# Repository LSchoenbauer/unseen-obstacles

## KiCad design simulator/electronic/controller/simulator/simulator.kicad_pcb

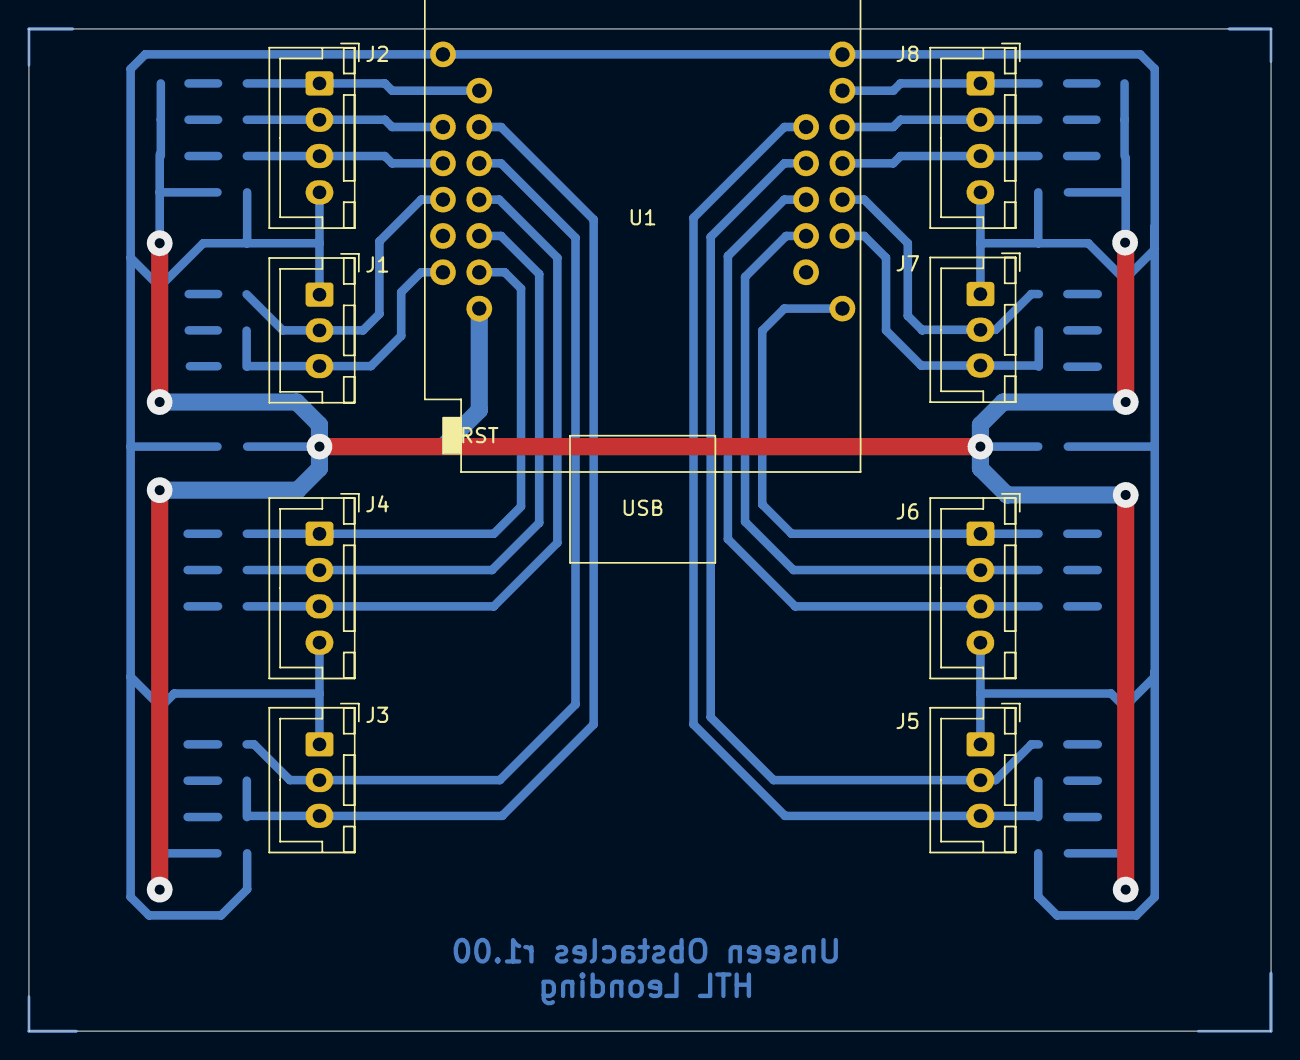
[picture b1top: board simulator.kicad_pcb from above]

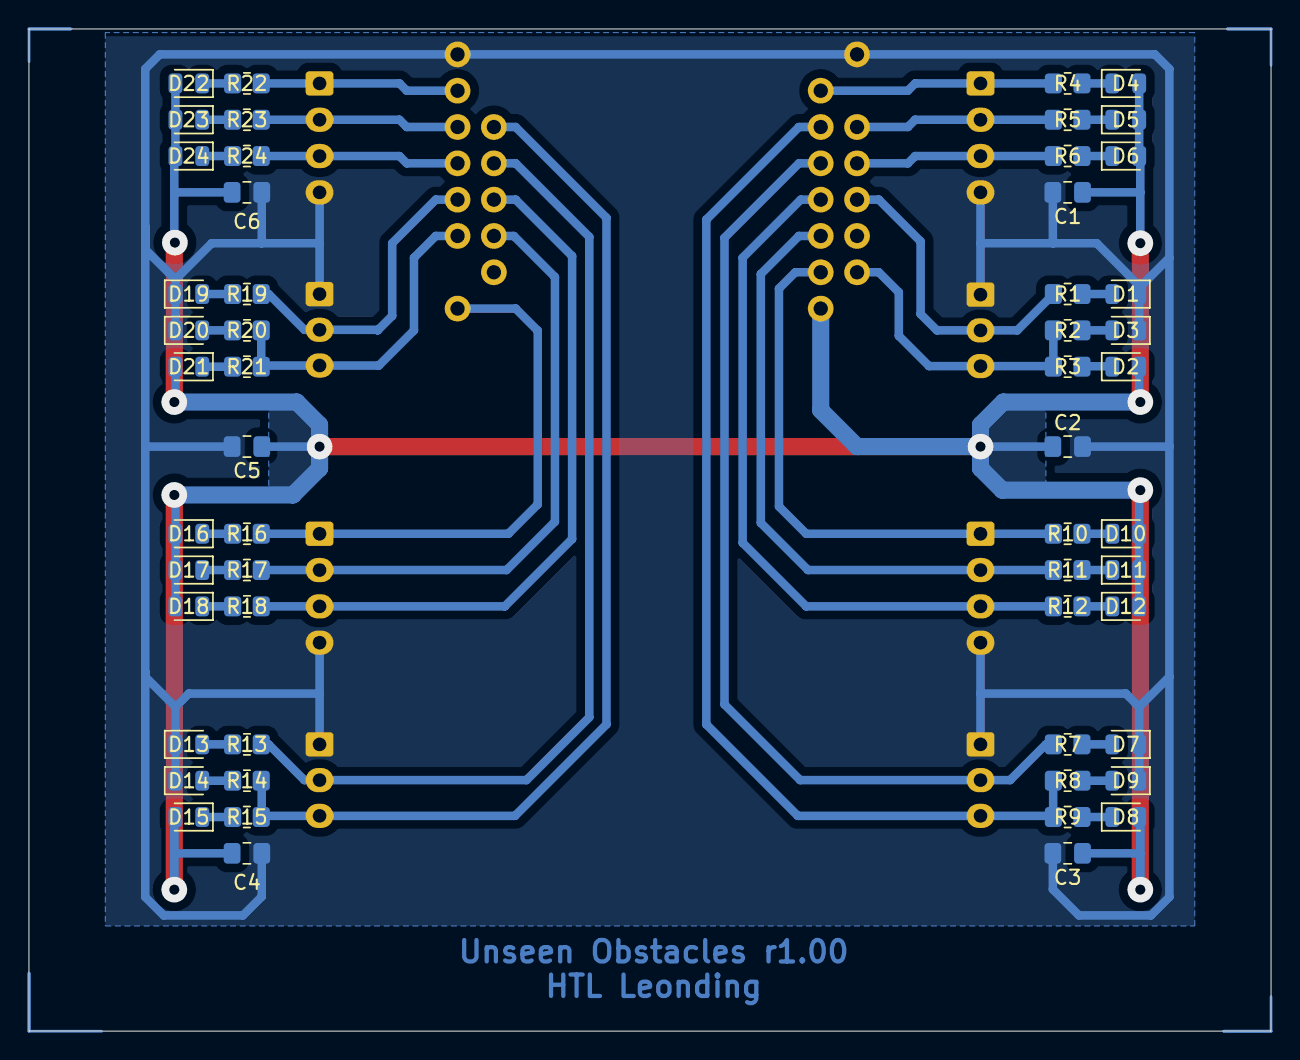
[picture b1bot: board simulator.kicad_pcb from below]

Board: 2 copper layers, 86.9 x 70.1 mm, 63 parts (54 on the bottom side), 46 nets.

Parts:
C1, C2, C3, C4, C5, C6: 100n; C_0805_2012Metric_Pad1.18x1.45mm_HandSolder
D1, D7, D13, D19: LED_PULSE; LED_0805_2012Metric
D2, D8, D14, D20: LED_UP; LED_0805_2012Metric
D3, D9, D15, D21: LED_DOWN; LED_0805_2012Metric
D4, D10, D16, D22: LED_TOP; LED_0805_2012Metric
D5, D11, D17, D23: LED_CENTER; LED_0805_2012Metric
D6, D12, D18, D24: LED_BTM; LED_0805_2012Metric
J1, J3, J5, J7: Conn_01x03_Socket; JST_XH_B3B-XH-A_1x03_P2.50mm_Vertical
J2, J4, J6, J8: Conn_01x04_Socket; JST_XH_B4B-XH-A_1x04_P2.54mm_Vertical
R1, R2, R3, R4, R5, R6, R7, R8, R9, R10, R11, R12, R13, R14, R15, R16, R17, R18, R19, R20, R21, R22, R23, R24: 150R; R_0805_2012Metric_Pad1.20x1.40mm_HandSolder
U1: ESP32 D1 Mini; ESP32_D1_mini

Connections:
3V3: C1.1, C2.1, C3.1, C4.1, C5.1, C6.1, D3.2 (A), D4.2 (A), D5.2 (A), D6.2 (A), D9.2 (A), D10.2 (A), D11.2 (A), D12.2 (A), D15.2 (A), D16.2 (A), D17.2 (A), D18.2 (A), D21.2 (A), D22.2 (A), D23.2 (A), D24.2 (A), U1.16 (3V3)
GND: C1.2, C2.2, C3.2, C4.2, C5.2, C6.2, D1.1 (K), D2.1 (K), D7.1 (K), D8.1 (K), D13.1 (K), D14.1 (K), D19.1 (K), D20.1 (K), J1.1, J2.4, J3.1, J4.4, J5.1, J6.4, J7.1, J8.4, U1.1 (GND), U1.22 (GND)
M1_DIR: J1.3, R2.2, R3.2, U1.13 (IO_14/TMS)
M1_PULSE: J1.2, R1.2, U1.9 (IO_33)
M1_SW_BTM: J2.3, R6.2, U1.7 (IO_35)
M1_SW_CTR: J2.2, R5.2, U1.5 (IO_39/SVN)
M1_SW_TOP: J2.1, R4.2, U1.4 (IO_36/SVP/A0)
M2_DIR: J3.3, R8.2, R9.2, U1.6 (IO_26/D0)
M2_PULSE: J3.2, R7.2, U1.8 (IO_18/D5)
M2_SW_BTM: J4.3, R12.2, U1.10 (IO_19/D6)
M2_SW_CTR: J4.2, R11.2, U1.12 (IO_23/D7)
M2_SW_TOP: J4.1, R10.2, U1.14 (IO_05/D8)
M3_DIR: J5.3, R14.2, R15.2, U1.25 (IO_22/D1/SCL)
M3_PULSE: J5.2, R13.2, U1.27 (IO_21/D2/SDA)
M3_SW_BTM: J6.3, R18.2, U1.29 (IO_17/D3)
M3_SW_CTR: J6.2, R17.2, U1.31 (IO_16/D4)
M3_SW_TOP: J6.1, R16.2, U1.36 (IO_02)
M4_DIR: J7.3, R20.2, R21.2, U1.32 (IO_04)
M4_PULSE: J7.2, R19.2, U1.30 (IO_12/TDI)
M4_SW_CTR: J8.2, R23.2, U1.26 (IO_25)
M4_SW_LEFT: J8.1, R22.2, U1.24 (IO_27)
M4_SW_RIGHT: J8.3, R24.2, U1.28 (IO_32)
unnamed: D1.2 (A), R1.1
unnamed: D2.2 (A), R2.1
unnamed: D3.1 (K), R3.1
unnamed: D4.1 (K), R4.1
unnamed: D5.1 (K), R5.1
unnamed: D6.1 (K), R6.1
unnamed: D7.2 (A), R7.1
unnamed: D8.2 (A), R8.1
unnamed: D9.1 (K), R9.1
unnamed: D10.1 (K), R10.1
unnamed: D11.1 (K), R11.1
unnamed: D12.1 (K), R12.1
unnamed: D13.2 (A), R13.1
unnamed: D14.2 (A), R14.1
unnamed: D15.1 (K), R15.1
unnamed: D16.1 (K), R16.1
unnamed: D17.1 (K), R17.1
unnamed: D18.1 (K), R18.1
unnamed: D19.2 (A), R19.1
unnamed: D20.2 (A), R20.1
unnamed: D21.1 (K), R21.1
unnamed: D22.1 (K), R22.1
unnamed: D23.1 (K), R23.1
unnamed: D24.1 (K), R24.1

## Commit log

2025-07-04 added CAD models and documentation for simulator hardware
2025-07-12 added new connecting piece between scissor lift and stepper motor with 8mm shaft
2025-07-21 added ESP32 datasheets added kicad models, footprints, and symbols added ESP32-Arduino project for trying steppers added oscilloscope measurements of stepper pins
2025-08-06 Added description and evaluation report for mechanical lifting devices
2025-09-24 add simulator
2025-09-29 add: simulator
2025-09-29 design schematics
2025-10-01 added datasheets for LEDs and Steppers
2025-10-01 added 3D models of RGB LED
2025-10-06 update simulator
2025-10-06 added temp files to gitignore
2025-10-06 enhanced gitignore
2025-10-15 shaped schematic and PCB added printed documentation of PCB
2025-10-15 finalized schematics and PCB
2025-10-16 added measurement pictures
2025-10-17 update Platine (Vais)
2025-10-17 completed draft of stepper mounting sheets
2025-10-18 added stabilization Cos and alternative text
2025-10-19 made PDB singlesided, added stabilization capacitors and label
2025-10-19 completed stepper mount
2025-10-20 added bearing and washer
2025-10-20 prolonged seam and simplified mounting bracket for switches
2025-10-21 add writing-folder
2025-10-21 add files from tamplate
2025-10-21 add .gitignore
2025-10-21 create section cybersickness
2025-10-27 added mover parts: slide bearings and distance washers, switch bracket added printable models for all parts o print added cutting template for metal sheet parts added lifting jack model
2025-10-28 ChairController and PCBTester started
2025-10-28 add: buttons for motors
2025-10-28 added rear bearing for chair
2025-10-29 update: MoverDriver
2025-10-29 update: MoverDriver functionality
2025-11-08 coding session 29th of October, started ChairController
2025-11-10 cleaned up wires
2025-11-10 added coupling adapter for jack to stepper
2025-11-11 update: MoverDriver, begin Position Calibration code
2025-11-11 optimized scissor jack coupling
2025-11-12 removed obsolete models
2025-11-12 made washer for slide bearing broader
2025-11-12 optimized scissor jack to stepper coupling
2025-11-12 improved and extended PCB test application
2025-11-17 added mounting parts for flat mounting of power supply
2025-11-18 added pin config header file for mover driver
2025-11-19 Added CAD models for upright mounting of power supply
2025-11-19 refactor MoverDriver config
2025-11-19 added mounting brackets with extended screw holes and screw(hole)extender for M4
2025-11-19 update MoverDriver timer
2025-11-20 remote controlling stepper driver
2025-12-17 feat: web-app lifts and lowers wheelchair
2025-12-17 update Moverdriver
2025-12-17 update: MoverDriver timer
2025-12-26 update: coversheet
2025-12-27 add pics to project
2025-12-27 add vr-world.tex
2025-12-27 add vr-world section to thesis.tex
2025-12-30 update section interaktion in vr
2025-12-30 add hardware-prototyp.tex
2025-12-31 update: cyber_sickness
2025-12-31 update: citation for cyber_sickness
2025-12-31 update: references in cyber_sickenss chapter
2025-12-31 fix: citation 9
2026-01-09 feat: ChairController - move stepper
2026-01-12 udp server
2026-01-28 update: ChairController
2026-01-29 fixed control of pulse pin for stepper improved ISR debugging
2026-02-02 added multi-threading for logging
2026-02-02 modified Antriebswalze to support coating with flex material and mounting using a wedge
2026-02-02 fixed indentations
2026-02-02 prepared data and controller for multi-tasking
2026-02-02 fixed platformio.ini dependencies (typo) and the return value of CommandData::Acquire
2026-02-02 fixed platformio.ini dependencies (typo)
2026-02-02 removed inline initialization
2026-02-04 added condition for "AdjustToSimulation" minor formatting improvements
2026-02-04 implemented multi-tasking mover driver fixed multi-tasking logging
2026-02-05 fixed microstep configuration
2026-02-06 web-app responsive
2026-02-06 made chair controller asynchronous and attached it to the main task moved UDP server to specific task improved limit stop in mover drivers
2026-02-07 update writing
2026-02-10 update webapp
2026-02-11 update: stepper movement on command helper functions
2026-02-11 update: clicker implementation
2026-02-12 added task info print-outs
2026-02-15 update: hardware-prototyp.tex
2026-02-16 update: writiing hardware-prototyp
2026-02-22 added dependent libraries for UDP server and task management
2026-02-22 refactored UDP server and TaskMgmt to libs and added dependencies. added build target for custom FreeRTOS to enable task table information. minor fixes and clean-ups
2026-02-22 fixed IP address setting for WiFi AP
2026-02-25 added simple UDP client for testing UDP server.
2026-02-25 enhanced ignorelist
2026-02-26 update writing: hardware-prototyp
2026-02-26 add: handbuch.tex
2026-02-26 add: ideenfindung.tex
2026-02-26 update: Umfeldanalyse
2026-03-07 Added simple client for testing data transmission via UDP
2026-03-09 added handshake and heartbeat to UDP transfer protocol added tagging support for logging extracted UDP server implementation from Arduino to lib, because Arduino library is not working with patched F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
2026-03-09 added handshake / heartbeat and refactored client.
2026-03-11 feat: started communication vr hardware
2026-03-12 update: communication vr hardware
2026-03-15 update: communication vr hw
2026-03-15 feat: immersion section
2026-03-15 update: immersion
2026-03-16 update: sources
2026-03-17 abstract
2026-03-17 quellen hinzugefügt
2026-03-18 feat: summary
2026-03-19 uploaded updated thesis.pdf from 18th of march
2026-03-19 update pdf
2026-03-19 update: pdf
2026-03-31 finalize: writing
2026-04-01 update: name spacing in oath.tex
2026-04-01 update: code sources
2026-04-01 fix: spelling
2026-04-01 update: handbuch
2026-04-01 update: remove redundant pages
2026-04-20 feat: more button functionality
